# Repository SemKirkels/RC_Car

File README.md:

# RC Car

## Hardware Block Design

## Software Block Design

## Pinout

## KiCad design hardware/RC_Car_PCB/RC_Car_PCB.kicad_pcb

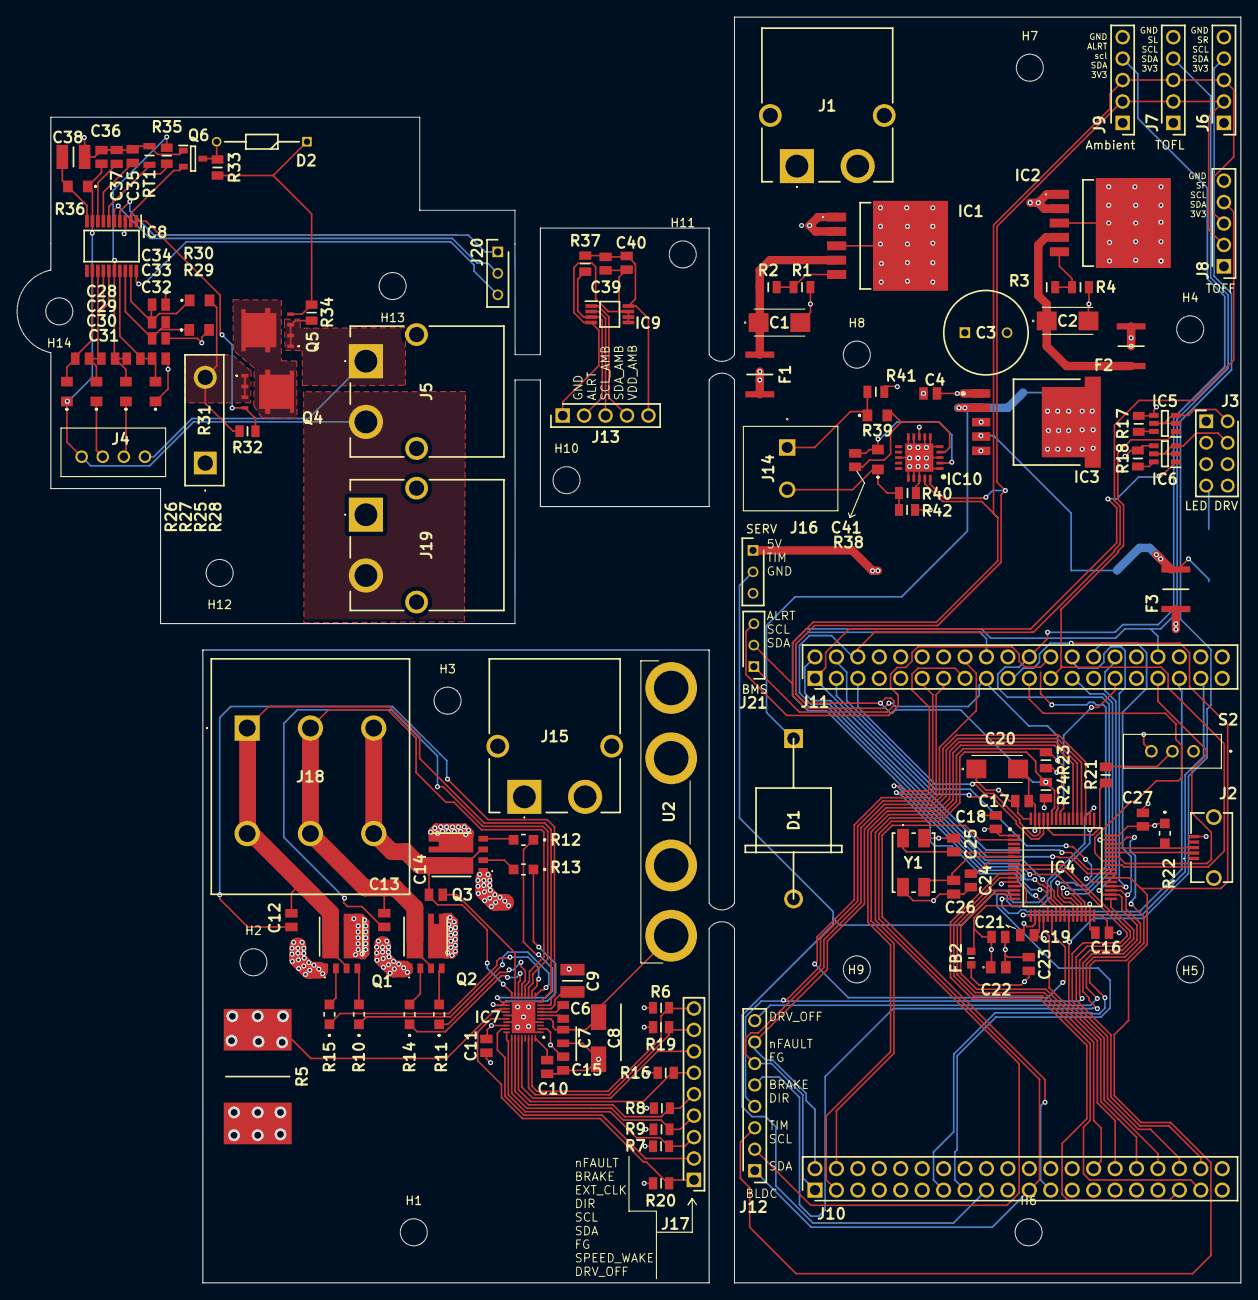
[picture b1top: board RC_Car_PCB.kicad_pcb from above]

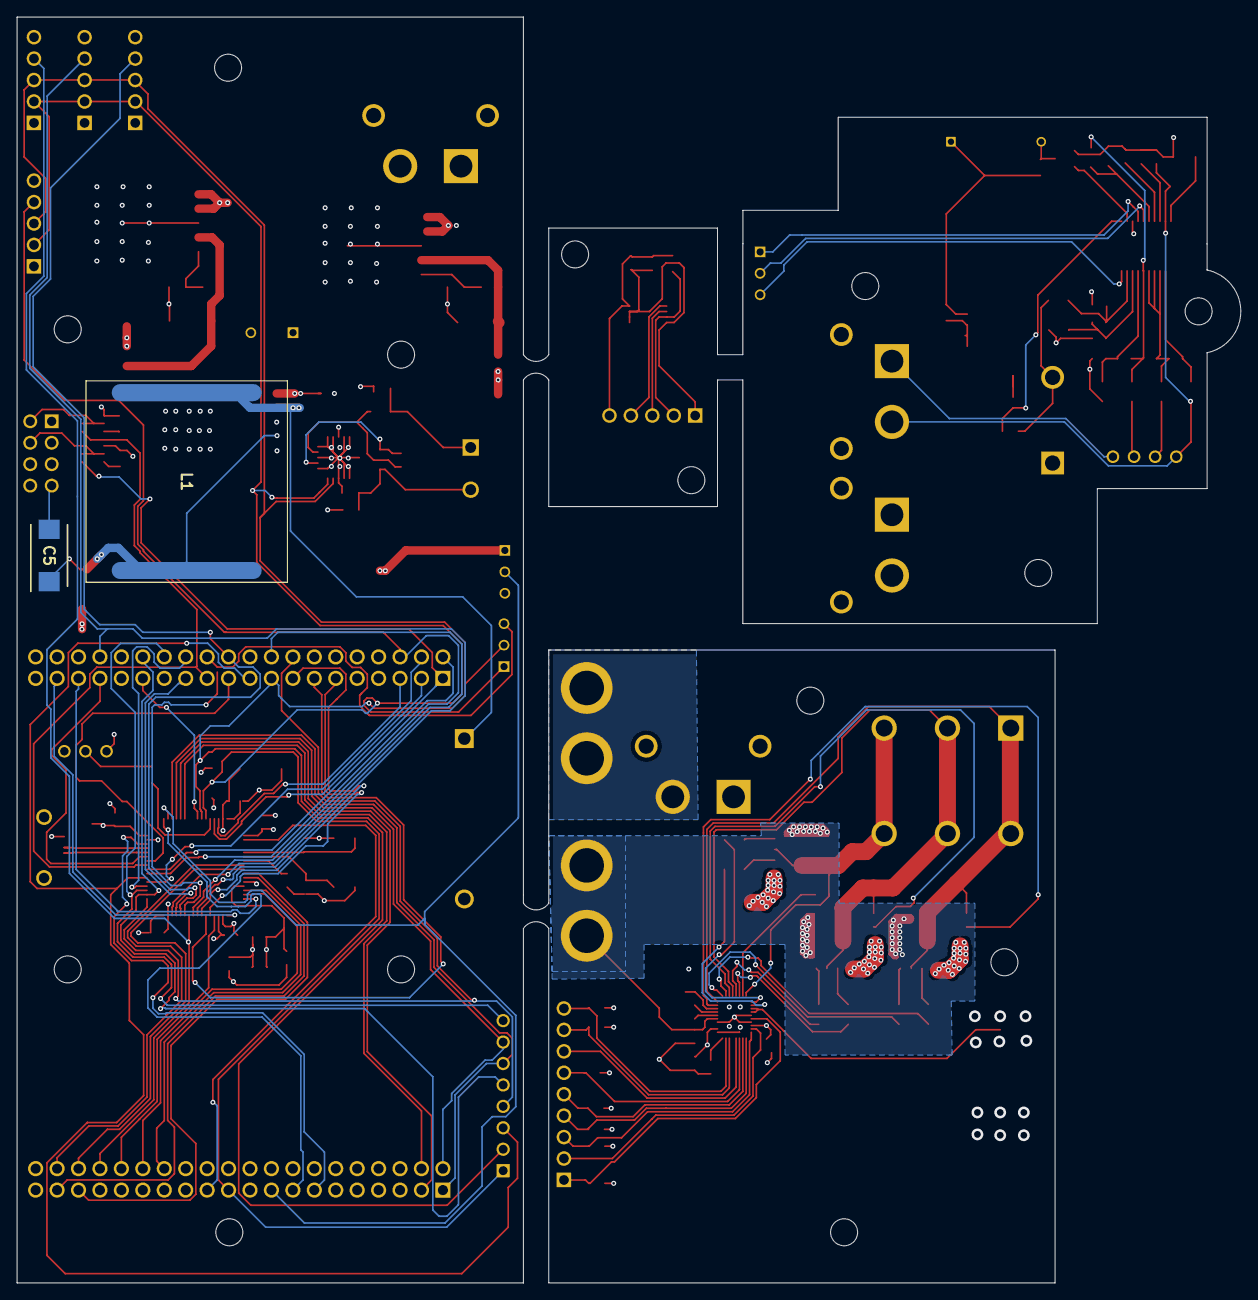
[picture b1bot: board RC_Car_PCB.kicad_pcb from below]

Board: 4 copper layers, 145.0 x 150.0 mm, 145 parts (2 on the bottom side), 131 nets.

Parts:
C1, C2, C20: 10µF; T491C
C3: 680µF; CAPPRD500W65D1000H1750
C4, C16, C17, C18, C19, C24, C27, C32, C33, C34, C39, C41: 100nF; CAPC2012X140N
C5: 220µF; CAPPM7344X310N
C6: 470nF; CAPC2012X90N
C7: 100nF; CAPC2013X94N
C8: 22µF; EXV106M035A9DAA
C9, C38: 10µF; CAPC3225X285N
C10, C11, C12, C13, C14, C15, C21, C23, C28, C29, C30, C31, C35, C36, C40: 1µF; CAPC2012X94N
C22: 10nF; C0805
C25, C26: 18pF; CAPC2012X98N
C37: 4.7µF; CAPC2012X145N
D1: 1N5824
D2: 1N4148; DIOAD1068W53L380D172
F1, F2, F3: PTS18126V300; FUSC4632X120N
FB2: 600; BEADC1608X95N
H1, H2, H3: MH_Gate_driver; MountingHole_3.2mm_M3_DIN965
H4, H5, H6, H7, H8, H9, H10, H11, H12, H13, H14: MH_STM; MountingHole_3.2mm_M3_DIN965
IC1, IC2: LT1764EQ#PBF; LT1764EQPBF
IC3: LM2596SX-5.0_NOPB; KTT0005B
IC4: STM32L476RGT6TR; QFP50P1200X1200X160-64N
IC5, IC6: BCR421UW6Q-7; SOT95P285X140-6N
IC7: MCF8329A1IREER; QFN40P400X500X80-37N-D
IC8: BQ7692006PW; SOP65P640X120-20N
IC9: MCP9808-E_MS; SOP65P490X110-8N
IC10: MCP9600-E_MX; QFN65P500X500X100-21N-D
J1, J5, J15, J19: XT60PW-M; XT60PWM
J2: ZX62WD1-B-5PC; ZX62WD1B5PC
J3: XG8T-0831; HDRV8W64P254_2X4_1020X500X680P
J4: B4B-XH-A_LF__SN_; B4BXHALFSN
J6, J7, J8, J9, J13: 22-28-4054; HDRV5W66P0X254_1X5_1270X249X1067P
J10, J11: M20-7832042; RHDR40W70P254_2X20_5120X504X850P
J12: 22-28-4083; HDRV8W87P0X254_1X8_2032X249X863P
J14: 1711026
J16, J20, J21: M20-9990345; HDRV3W64P0X254_1X3_762X254X864P
J17: 22-30-3093; HDRV9W66P0X254_1X9_2286X249X1258P
J18: 221391-0003; 2213910003
L1: 38µH; PE54040SNL
Q1, Q2, Q3: PSMN4R2-40VSHX; PSMN4R240VSHX
Q4, Q5: SQJ422EP-T1_BE3; SQJ422EPT1_BE3
Q6: BSS84; SOT95P240X120-3N
R1, R4: 3600; RESC2012X50N
R2, R3: 6200; RESC2012X50N
R5: 300µ; RESC15078X155N
R6, R7, R8, R9: 5.1K; RESC2012X60N
R10, R11, R12, R15: 33; ERA6AEB101V
R13, R14: 30; ERA6AEB101V
R16, R19, R20, R23, R24, R37: 4.7k; RESC2013X65N
R17, R18: 8.06; RESC2012X60N
R21: 10k; RESC2012X70N
R22: 1k5; ERA6AEB101V
R25, R26, R27, R28, R29, R30, R36, R38, R39: 100; ERJP06D1000V
R31: 0.002; FWP21830CR002F
R32, R33, R34: 1M; RESC2012X65N
R35: 20k; RESC2012X65N
R40, R41: 2M; RESC2012X50N
R42: CRCW08051M00JNEAHP; RESC2012X60N
RT1: 10k; THRMC2012X95N
S2: EG1218
U2: 3555-2; 35552
Y1: 8MHz; EA5070LA128000MTR

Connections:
3V3 LDO: F2.2, IC10.8 (VDD), J3.1, J3.3, J6.1, J7.1, J8.1, J9.1, R42.2
3V3 STM: C16.1, C17.1, C18.1, C19.1, C20.1 (+), C21.1, C22.1, C23.1, C27.1, F1.2, FB2.1, FB2.2, IC4.1 (VBAT), IC4.13 (VDDA/VREF+), IC4.19 (VDD_1), IC4.32 (VDD_2), IC4.48 (VDDUSB), IC4.64 (VDD_3), J10.5, J10.33, R22.1, R23.1, R24.1, S2.3 (NO)
5V: F3.2, J16.1
11V1: C3.1 (+), C4.1, C7.1 (C1), C8.1 (+), IC1.1 (~SHDN), IC1.2 (IN), IC2.1 (~SHDN), IC2.2 (IN), IC3.1 (VIN), IC7.5 (PVDD), J1.2, Q1.5 (D1_1), Q1.6 (D1_2), Q1.10 (D1_3), Q2.5 (D1_1), Q2.6 (D1_2), Q2.10 (D1_3), Q3.5 (D1_1), Q3.6 (D1_2), Q3.10 (D1_3), U2.3, U2.4
/LedDriver/LED_driver1: IC5.2 (OUT_1), IC5.3 (OUT_2), IC5.5 (OUT_3), J3.2
/LedDriver/LED_driver2: IC6.2 (OUT_1), IC6.3 (OUT_2), IC6.5 (OUT_3), J3.4
/MCU/ADC1_IN1: IC4.8 (PC0), J10.38
/MCU/ADC1_IN2: IC4.9 (PC1), J10.36
/MCU/ADC1_IN3: IC4.10 (PC2), J10.35
/MCU/ADC1_IN4: IC4.11 (PC3), J10.37
/MCU/ALERT_AMBIENT_TEMP: IC4.28 (PB2), J9.4, J11.22
/MCU/ALERT_BMC: IC4.27 (PB1), J11.24, J21.3
/MCU/BLDC_BRAKE: IC4.34 (PB13), J11.30, J12.5
/MCU/BLDC_DIR: IC4.33 (PB12), J11.16, J12.4
/MCU/BLDC_Drvoff: IC4.35 (PB14), J11.28, J12.8
/MCU/BLDC_FG: IC4.51 (PC10), J10.1, J12.6
/MCU/BLDC_PWM_TIM3_CH2: IC4.38 (PC7), J11.19, J12.3
/MCU/BLDC_nFAULT: IC4.52 (PC11), J10.2, J12.7
/MCU/BOOT0: IC4.60 (BOOT0), R21.2
/MCU/DAC1_OUT1: IC4.20 (PA4), J10.32
/MCU/HSE_IN: C25.1, IC4.5 (PH0-OSC_IN_(PH0)), Y1.1 (CRYSTAL_1)
/MCU/HSE_OUT: C26.1, IC4.6 (PH1-OSC_OUT_(PH1)), Y1.3 (CRYSTAL_2)
/MCU/I2C_SCL_STM: IC4.58 (PB6), IC10.19 (SCL), J6.3, J7.3, J8.3, J9.3, J11.17, J12.2, J21.2, R23.2
/MCU/I2C_SDA_STM: IC4.59 (PB7), IC10.20 (SDA), J6.2, J7.2, J8.2, J9.2, J10.21, J12.1, J21.1, R24.2
/MCU/LED_Front: IC4.41 (PA8), IC5.1 (EN), J11.23
/MCU/LED_Rear: IC4.40 (PC9), IC6.1 (EN), J11.1
/MCU/NRST: C24.1, IC4.7 (NRST)
/MCU/PA2: IC4.16 (PA2), J11.35
/MCU/PA3: IC4.17 (PA3), J11.37
/MCU/PB5: IC4.57 (PB5), J11.29
/MCU/PB8: IC4.61 (PB8), J11.3
/MCU/PB9: IC4.62 (PB9), J11.5
/MCU/PB10: IC4.29 (PB10), J11.25
/MCU/PB11: IC4.30 (PB11), J11.18
/MCU/PB15: IC4.36 (PB15), J11.26
/MCU/PC6: IC4.37 (PC6), J11.4
/MCU/PC8: IC4.39 (PC8), J11.2
/MCU/PC13: IC4.2 (PC13), J10.23
/MCU/SERVO_PWM_TIM2_CH1: IC4.50 (PA15_(JTDI)), J10.17, J16.2
/MCU/SPI1_MISO: IC4.22 (PA6), J11.13
/MCU/SPI1_MOSI: IC4.23 (PA7), J11.15
/MCU/SPI1_SCK: IC4.21 (PA5), J11.11
/MCU/SWCLK: IC4.49 (PA14_(JTCK-SWCLK)), J10.15
/MCU/SWDIO: IC4.46 (PA13_(JTMS-SWDIO)), J10.13
/MCU/SW_BOOT0: R21.1, S2.2 (COMM)
/MCU/TOFxShut_Front: IC4.25 (PC5), J8.4, J11.6
/MCU/TOFxShut_Left: IC4.24 (PC4), J7.4, J11.34
/MCU/TOFxShut_Right: IC4.26 (PB0), J6.4, J10.34
/MCU/UART4_RX: IC4.15 (PA1), J10.30
/MCU/UART4_TX: IC4.14 (PA0), J10.28
/MCU/UART5_RX: IC4.54 (PD2), J10.4
/MCU/UART5_TX: IC4.53 (PC12), J10.3
/MCU/USART1_RX: IC4.43 (PA10), J11.33
/MCU/USART1_TX: IC4.42 (PA9), J11.21
/MCU/USB_D+: IC4.45 (PA12), J2.3, R22.2
/MCU/USB_D-: IC4.44 (PA11), J2.2
/Power Electronics/AVDD: C11.1, C15.1, IC7.2 (VREG), IC7.26 (AVDD), R6.2, R7.2, R8.2, R9.2
/Power Electronics/BRAKE: IC7.34 (BRAKE), J17.8, R19.1
/Power Electronics/DIR: IC7.31 (DIR), J17.6, R16.1
/Power Electronics/DRVOFF: IC7.24 (DRVOFF), J17.1, R20.1
/Power Electronics/EXT_CLK: IC7.32 (EXT_CLK), J17.7
/Power Electronics/FG: IC7.28 (FG), J17.3, R7.1
/Power Electronics/M_A: C12.2, IC7.10 (SHA), J18.1, J18.2, Q1.3 (S1), Q1.7 (S1_D2_1), Q1.8 (S1_D2_2), Q1.9 (S1_D2_3)
/Power Electronics/M_B: C13.2, IC7.14 (SHB), J18.3, J18.4, Q2.3 (S1), Q2.7 (S1_D2_1), Q2.8 (S1_D2_2), Q2.9 (S1_D2_3)
/Power Electronics/M_C: C14.2, IC7.18 (SHC), J18.5, J18.6, Q3.3 (S1), Q3.7 (S1_D2_1), Q3.8 (S1_D2_2), Q3.9 (S1_D2_3)
/Power Electronics/NFAULT: IC7.35 (NFAULT), J17.9, R6.1
/Power Electronics/SCL_driver: IC7.30 (SCL), J17.5, R8.1
/Power Electronics/SDA_driver: IC7.29 (SDA), J17.4, R9.1
/Power Electronics/SPEED/WAKE: IC7.27 (SPEED/WAKE), J17.2
/Sensors/ALERT_AMB: IC9.3 (ALERT), J13.2, R37.2
/Sensors/ALERT_BMS: IC8.20 (ALERT), J20.3
/Sensors/GND(ambient): C39.2, C40.2, IC9.4 (GND), IC9.5 (A2), IC9.6 (A1), IC9.7 (A0), J13.1
/Sensors/LOAD+: C36.1, IC8.9 (REGSRC), J4.1, J5.2, J19.2, R26.1, R36.1
/Sensors/PACK-: J4.4, J5.1, Q5.1 (S_1), Q5.2 (S_2), Q5.3 (S_3), R34.2
/Sensors/SCL_Ambient: IC9.2 (SCL), J13.3
/Sensors/SCL_BMS: IC8.5 (SCL), J20.2
/Sensors/SDA_Ambient: IC9.1 (SDA), J13.4
/Sensors/SDA_BMS: IC8.4 (SDA), J20.1
/Sensors/TS1: C29.2, C30.1, IC8.16 (VC1), R25.2, R35.2
/Sensors/VDD_ambient: C39.1, C40.1, IC9.8 (VDD), J13.5, R37.1
/Sensors/cel1-2: J4.3, R25.1
/Sensors/cel2-3: J4.2, R27.1
GND: C1.2 (-), C2.2 (-), C3.2 (-), C4.2, C5.2 (-), C7.2 (C2), C8.2 (-), C9.2, C10.2, C11.2, C15.2, C16.2, C17.2, C18.2, C19.2, C20.2 (-), C21.2, C22.2, C23.2, C24.2, C25.2, C26.2, C27.2, C31.2, C32.1, C34.2, C35.2, C36.2, C37.2, C38.2, D1.2 (A), IC1.3 (GND_1), IC1.6 (GND_2), IC2.3 (GND_1), IC2.6 (GND_2), IC3.3 (GND), IC3.5 (~ON_/_OFF), IC3.6 (TAB_(GND)), IC4.12 (VSSA/VREF-), IC4.18 (VSS_1), IC4.31 (VSS_2), IC4.47 (VSS_3), IC4.63 (VSS_4), IC5.4 (GND), IC6.4 (GND), IC7.1 (DGND), IC7.4 (GND_1), IC7.23 (SN), IC7.25 (AGND), IC7.37 (GND_2), IC8.3 (VSS), IC10.1 (GND_1), IC10.3 (GND_2), IC10.5 (GND_3), IC10.6 (GND_4), IC10.7 (GND_5), IC10.9 (GND_6), IC10.10 (GND_7), IC10.13 (GND_8), IC10.16 (ADDR), IC10.17 (GND_9), IC10.18 (GND_10), IC10.21 (EP), J1.1, J1.3 (MH1), J1.4 (MH2), J2.5, J2.MH1, J2.MH2, J3.5, J3.6, J3.7, J3.8, J6.5, J7.5, J8.5, J9.5, J10.8, J10.19, J10.20, J10.22, J10.39, J10.40, J11.9, J11.20, J11.32, J11.39, J11.40, J15.1, J15.3 (MH1), J15.4 (MH2), J16.3, J19.1, Q6.1 (G), R1.2, R4.2, R5.2, R16.2, R17.2, R18.2, R19.2, R20.2, R28.1, R29.2, R31.1, R40.1, R41.1, RT1.2, S2.1 (NC), Y1.2 (COVER/GROUND_1), Y1.4 (COVER/GROUND_2)
unnamed: C1.1 (+), F1.1, IC1.4 (OUT), R2.1
unnamed: C2.1 (+), F2.1, IC2.4 (OUT), R3.1
unnamed: C5.1 (+), F3.1, IC3.4 (FEED_BACK), L1.2
unnamed: D1.1 (K), IC3.2 (OUTPUT), L1.1
unnamed: D2.2 (A), Q6.3 (D), R33.1
unnamed: D2.1 (K), Q5.4 (G), R33.2, R34.1
unnamed: IC1.5 (ADJ), R1.1, R2.2
unnamed: IC2.5 (ADJ), R3.2, R4.1
unnamed: IC5.6 (REXT), R17.1
unnamed: IC6.6 (REXT), R18.1
unnamed: C12.1, IC7.9 (BSTA)
unnamed: C13.1, IC7.13 (BSTB)
unnamed: C14.1, IC7.17 (BSTC)
unnamed: C6.2, IC7.7 (CPH)
unnamed: C6.1, IC7.6 (CPL)
unnamed: C10.1, IC7.36 (DVDD)
unnamed: IC7.11 (GHA), R10.1
unnamed: IC7.15 (GHB), R11.1
unnamed: IC7.19 (GHC), R12.1
unnamed: IC7.12 (GLA), R15.1
unnamed: IC7.16 (GLB), R14.1
unnamed: IC7.20 (GLC), R13.1
unnamed: C9.1, IC7.8 (GVDD)
unnamed: IC7.21 (LSS), IC7.22 (SP), Q1.1 (S2), Q2.1 (S2), Q3.1 (S2), R5.1
unnamed: C38.1, IC8.10 (BAT), R36.2
unnamed: C35.1, IC8.7 (CAP1)
unnamed: IC8.2 (CHG), Q6.2 (S)
unnamed: IC8.1 (DSG), Q4.4 (G), R32.1
unnamed: C37.1, IC8.8 (REGOUT)
unnamed: C33.2, C34.1, IC8.19 (SRN), R30.1
unnamed: C32.2, C33.1, IC8.18 (SRP), R29.1
unnamed: IC8.6 (TS1), R35.1, RT1.1
unnamed: C30.2, C31.1, IC8.17 (VC0), R28.2
unnamed: C28.2, C29.1, IC8.13 (VC4), IC8.14 (VC3), IC8.15 (VC2), R27.2
unnamed: C28.1, IC8.12 (VC5), R26.2
unnamed: C41.1, IC10.2 (VIN+), R38.2
unnamed: C41.2, IC10.4 (VIN-), R39.2
unnamed: J14.1, R39.1, R41.2
unnamed: J14.2, R38.1, R40.2, R42.1
unnamed: J15.2, U2.1, U2.2
unnamed: Q1.4 (G1), R10.2
unnamed: Q1.2 (G2), R15.2
unnamed: Q2.4 (G1), R11.2
unnamed: Q2.2 (G2), R14.2
unnamed: Q3.4 (G1), R12.2
unnamed: Q3.2 (G2), R13.2
unnamed: Q4.5 (D_1), Q4.6 (D_2), Q4.7 (D_3), Q4.8 (D_4), Q5.5 (D_1), Q5.6 (D_2), Q5.7 (D_3), Q5.8 (D_4)
unnamed: Q4.1 (S_1), Q4.2 (S_2), Q4.3 (S_3), R30.2, R31.2, R32.2

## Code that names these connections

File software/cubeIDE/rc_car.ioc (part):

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Mcu.Name=STM32L476R(C-E-G)Tx
Mcu.Package=LQFP64
Mcu.UserName=STM32L476RGTx
PA0.Mode=Asynchronous
PA0.Signal=UART4_TX
PA1.Mode=Asynchronous
PA1.Signal=UART4_RX
PA10.Mode=Asynchronous
PA10.Signal=USART1_RX
PA11.Mode=Device_Only
PA11.Signal=USB_OTG_FS_DM
PA12.Mode=Device_Only
PA12.Signal=USB_OTG_FS_DP
PA15\ (JTDI).GPIOParameters=GPIO_Label
PA15\ (JTDI).GPIO_Label=TIM2_CH1 (Servo PWM)
PA15\ (JTDI).Signal=S_TIM2_CH1
PA9.Mode=Asynchronous
PA9.Signal=USART1_TX
PB0.GPIOParameters=GPIO_Label
PB0.GPIO_Label=TOF xshut Right
PB0.Signal=GPIO_Output
PB1.GPIOParameters=GPIO_Label
PB1.GPIO_Label=Alert_BMC
PB1.Signal=GPIO_Input
PB12.GPIOParameters=GPIO_Label
PB12.GPIO_Label=BLDC Dir
PB12.Signal=GPXTI12
PB13.GPIOParameters=GPIO_Label
PB13.GPIO_Label=BLDC Brake
PB13.Signal=GPIO_Output
PB14.GPIOParameters=GPIO_Label
PB14.GPIO_Label=BLDC Drvoff
PB14.Signal=GPIO_Output
PB2.GPIOParameters=GPIO_Label
PB2.GPIO_Label=Alert_Ambient_Temp
PB2.Signal=GPIO_Input
PB6.Mode=I2C
PB6.Signal=I2C1_SCL
PB7.Mode=I2C
PB7.Signal=I2C1_SDA
PC10.GPIOParameters=GPIO_Label
PC10.GPIO_Label=BLDC FG
PC10.Signal=GPIO_Input
PC11.GPIOParameters=GPIO_Label
PC11.GPIO_Label=BLDC NFault
PC11.Signal=GPIO_Input
PC4.GPIOParameters=GPIO_Label
PC4.GPIO_Label=TOF xshut Left
PC4.Signal=GPIO_Output
PC5.GPIOParameters=GPIO_Label
PC5.GPIO_Label=TOF xshut Front
PC5.Signal=GPIO_Output
PC7.GPIOParameters=GPIO_Label
PC7.GPIO_Label=TIM3_CH2 (BLDC PWM)
PC7.Signal=S_TIM3_CH2
PC8.GPIOParameters=GPIO_Label
PC8.GPIO_Label=LED Front
PC8.Signal=GPIO_Output
PC9.GPIOParameters=GPIO_Label
PC9.GPIO_Label=LED Rear
PC9.Signal=GPIO_Output
RCC.HSE_VALUE=8000000
RCC.SYSCLKFreq_VALUE=80000000
RCC.SYSCLKSource=RCC_SYSCLKSOURCE_PLLCLK
board=custom

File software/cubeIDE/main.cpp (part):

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	TIM_CHANNEL_1,
	/* LEDs */
    GPIOC,
	LED_Front_Pin,
    GPIOC,
	LED_Rear_Pin,
	/* Motor driver */
	&htim3,
	TIM_CHANNEL_2,
	GPIOB,
	BLDC_Dir_Pin,
	GPIOB,
	BLDC_Brake_Pin,
	GPIOB,
	BLDC_Drvoff_Pin
);
/* Front LEDs */
GpioDrive leds_front(GPIOC, GPIO_PIN_8);
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  __HAL_RCC_GPIOD_CLK_ENABLE();

  /*Configure GPIO pin Output Level */
  HAL_GPIO_WritePin(GPIOC, TOF_xshut_Left_Pin|TOF_xshut_Front_Pin|LED_Front_Pin|LED_Rear_Pin, GPIO_PIN_RESET);

  /*Configure GPIO pin Output Level */
  HAL_GPIO_WritePin(GPIOB, TOF_xshut_Right_Pin|BLDC_Brake_Pin|BLDC_Drvoff_Pin, GPIO_PIN_RESET);

  /*Configure GPIO pins : TOF_xshut_Left_Pin TOF_xshut_Front_Pin LED_Front_Pin LED_Rear_Pin */
  GPIO_InitStruct.Pin = TOF_xshut_Left_Pin|TOF_xshut_Front_Pin|LED_Front_Pin|LED_Rear_Pin;
  GPIO_InitStruct.Mode = GPIO_MODE_OUTPUT_PP;
  GPIO_InitStruct.Pull = GPIO_NOPULL;
  GPIO_InitStruct.Speed = GPIO_SPEED_FREQ_LOW;
  HAL_GPIO_Init(GPIOC, &GPIO_InitStruct);

  /*Configure GPIO pins : TOF_xshut_Right_Pin BLDC_Brake_Pin BLDC_Drvoff_Pin */
  GPIO_InitStruct.Pin = TOF_xshut_Right_Pin|BLDC_Brake_Pin|BLDC_Drvoff_Pin;
  GPIO_InitStruct.Mode = GPIO_MODE_OUTPUT_PP;
  GPIO_InitStruct.Pull = GPIO_NOPULL;
  GPIO_InitStruct.Speed = GPIO_SPEED_FREQ_LOW;
  HAL_GPIO_Init(GPIOB, &GPIO_InitStruct);

  /*Configure GPIO pins : Alert_BMC_Pin Alert_Ambient_Temp_Pin */
  GPIO_InitStruct.Pin = Alert_BMC_Pin|Alert_Ambient_Temp_Pin;
  GPIO_InitStruct.Mode = GPIO_MODE_INPUT;
  GPIO_InitStruct.Pull = GPIO_NOPULL;
  HAL_GPIO_Init(GPIOB, &GPIO_InitStruct);

  /*Configure GPIO pin : BLDC_Dir_Pin */
  GPIO_InitStruct.Pin = BLDC_Dir_Pin;
  GPIO_InitStruct.Mode = GPIO_MODE_IT_RISING;
  GPIO_InitStruct.Pull = GPIO_NOPULL;
  HAL_GPIO_Init(BLDC_Dir_GPIO_Port, &GPIO_InitStruct);

  /*Configure GPIO pins : BLDC_FG_Pin BLDC_NFault_Pin */
  GPIO_InitStruct.Pin = BLDC_FG_Pin|BLDC_NFault_Pin;
  GPIO_InitStruct.Mode = GPIO_MODE_INPUT;
  GPIO_InitStruct.Pull = GPIO_NOPULL;
  HAL_GPIO_Init(GPIOC, &GPIO_InitStruct);
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
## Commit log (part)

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2026-03-03 Create placeholder
2026-03-04 upload class templates
2026-03-09 [data visualisation] upload starting files
2026-03-15 BOM
    bill of material RC car
2026-03-15 datasheet components
    datasheet of possible components
2026-03-15 Create datasheet.md with driver and sensor links
    Added links to various drivers and sensors in the datasheet.
2026-03-15 remove temp file
2026-03-15 Rename datasheet.md to README.md
2026-03-18 Block design
2026-03-18 Add link to drv8306 datasheet
2026-03-18 Enhance README with block design section
    Added block design section with an image to README.
2026-03-22 Correct link formatting in README.md
    Fix markdown link formatting for batterySensor.
2026-03-22 Fix link formatting for batterySensor entry
2026-03-23 uitbreiding componenten lijst + datasheets
2026-03-23 Update README with new images and section titles
2026-03-23 Revise sensor and voltage regulator sections
    Updated sensor and component listings in README.
2026-03-23 Fix GPIO LedDriver link in README.md
2026-03-23 Fix formatting of links in README.md
2026-03-30 Added gamepad readout test code
2026-03-30 Removed typo from gitignore
2026-03-30 Update gamepad code
    Added code to send over UDP + debug rx code to check if data is send correctly
2026-03-31 Create rx_gamepad.ino
    Created base template for esp gamepad rx
2026-03-31 Update rx_gamepad.ino
    fixed negative values
2026-03-31 Update main.cpp
    Removed negative value bug
2026-04-01 Update README.md with preference for mcf8329a-q1
    Added preference note to the mcf8329a-q1 link.
2026-04-01 Add 5V Buck Converter link to README.md
2026-04-01 Update hardware block design image in README
2026-04-01 update name map
2026-04-01 Create gpioDrive.h
    Created gpio class
2026-04-07 Add MOSFET BMC section to README
    Added MOSFET BMC section with relevant product link.
2026-04-07 bill of material PCB design
    The key components for the PCB
2026-04-10 Update gpio class
    added rc_config file for hw config. solved gh conflict
2026-04-10 update esp tx
    Correct output format for stm to parse
2026-04-10 KiCad schematic
    Finished with the Power supply and started with the BLDC driver
2026-04-14 finished BLDC driver
2026-04-15 BLDC driver calculations
2026-04-24 Upload parser code
    minor changed are still needed (polling rate)
2026-04-26 Upload steering class + Update Car class
2026-04-27 Upload motor class + added comments
2026-04-29 schematic design RC_CAR
2026-04-29 Create branch + changes sensors
2026-04-29 Removed magic numbers
2026-04-29 update components
    fixed footprints and components
2026-04-30 Upload readme + removed more magical numbers.
2026-04-30 mechanical design
2026-04-30 Fusion360 project
2026-04-30 changes Fusion design
    changed tolerances
2026-04-30 Upload I2C class + VL53L1x class.
    WIP VL53L0x + TOF task
2026-05-01 Upload ambient temp class (mcp9808) + start motor temp class (mcp9600)
2026-05-02 Update mcp9600 class
2026-05-04 Removed Typos from mcp9600 + upload vl53l0x class
2026-05-04 Start bms class + fixed error mcp9600
2026-05-05 Start BMS code
    WIP ReadGainOffset
2026-05-05 Removed unused functions
2026-05-12 changes PCB design and schematic
2026-05-15 restructure folders + finished ToF task for Vl53l0x sensors
2026-05-16 Update ToF task + health task + I2C DMA
    ToF task is debugged and confirmed operation for the vl53l0x, health task is created but not finished, i2c DMA is debugged and awaiting implementation in the sensor classes.
2026-05-16 converted sensor functions to use DMA
2026-05-16 Fixed a git issue
2026-05-17 start data visualisation
2026-05-17 resolved merge conflict
2026-05-17 Upload important config files
2026-05-17 complete layout RC_Car
2026-05-19 final adjustments

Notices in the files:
software/cubeIDE/main.cpp:
Copyright (c) 2026 STMicroelectronics.
All rights reserved.
This software is licensed under terms that can be found in the LICENSE file
